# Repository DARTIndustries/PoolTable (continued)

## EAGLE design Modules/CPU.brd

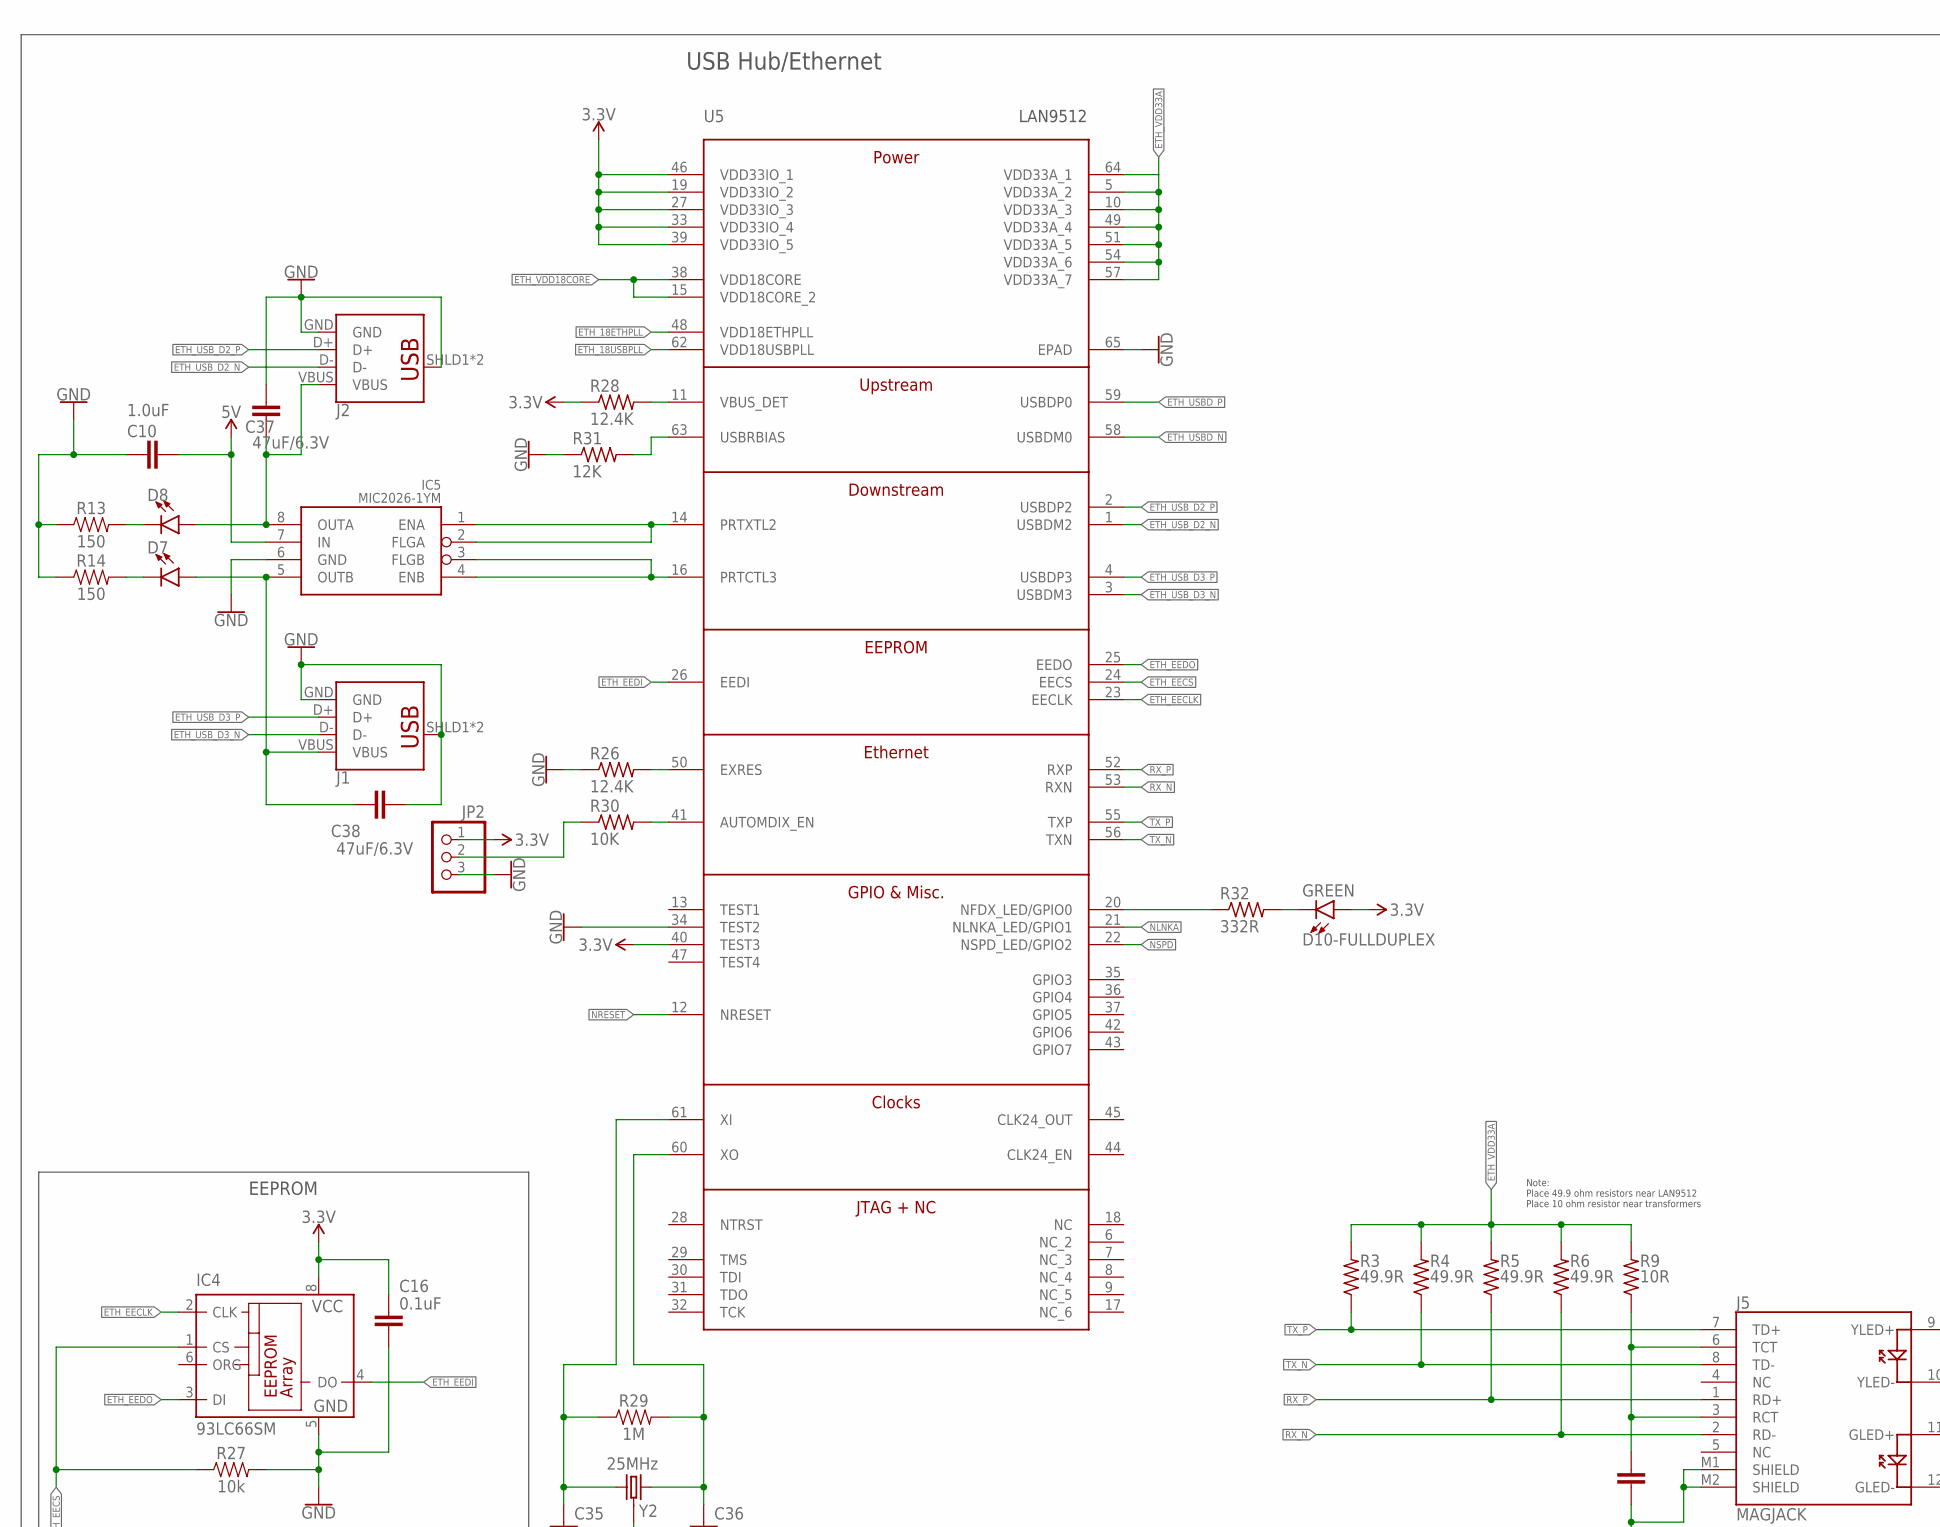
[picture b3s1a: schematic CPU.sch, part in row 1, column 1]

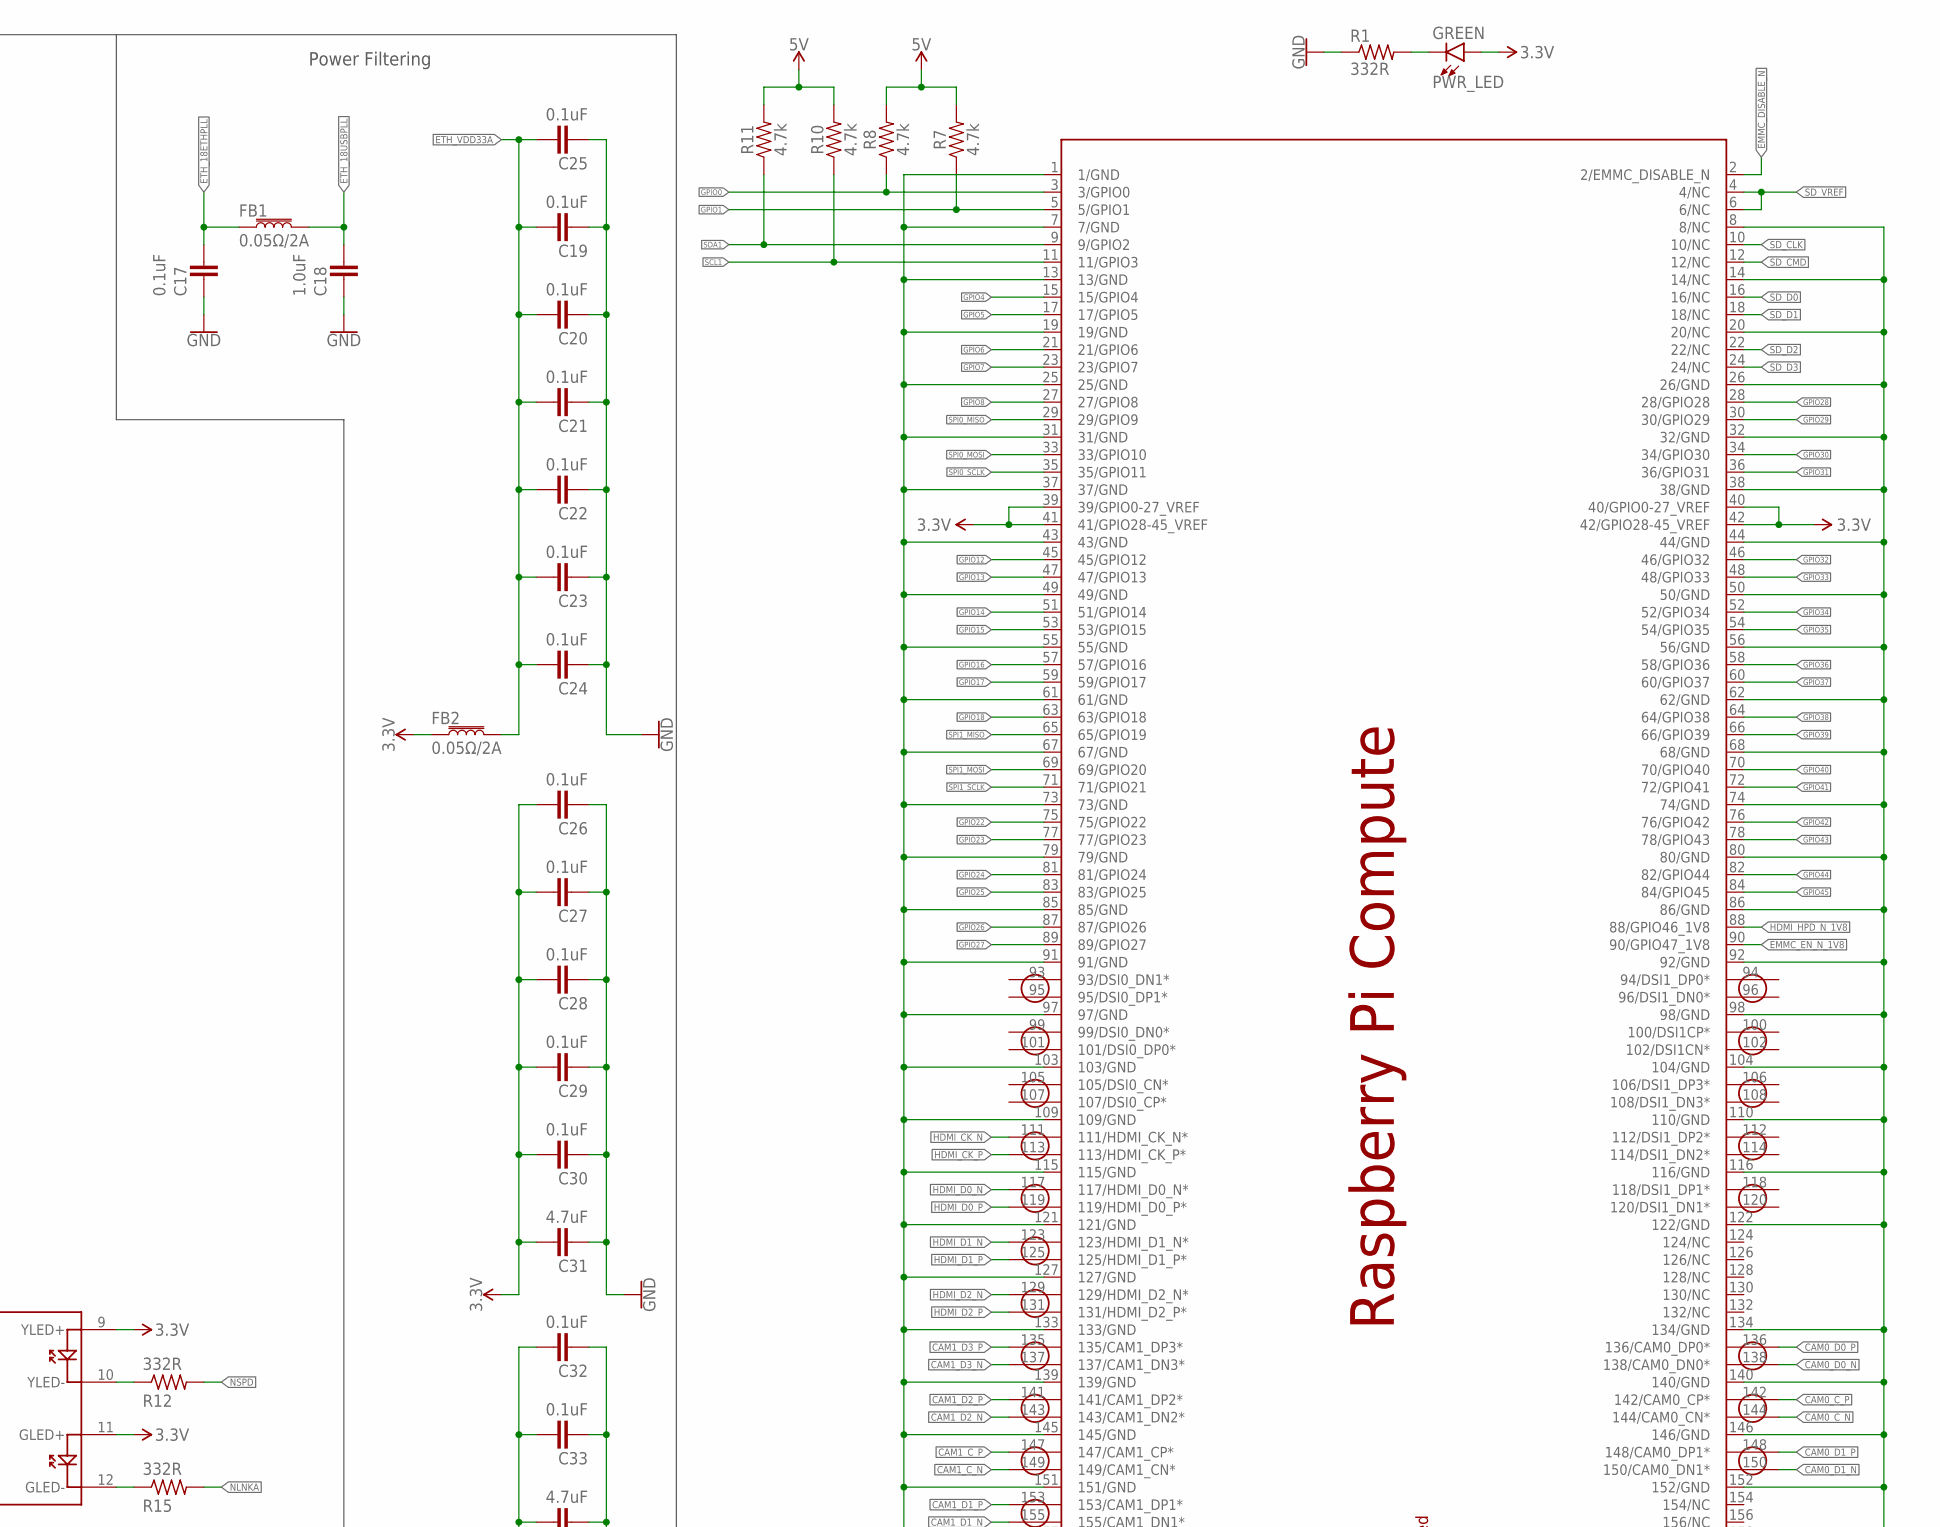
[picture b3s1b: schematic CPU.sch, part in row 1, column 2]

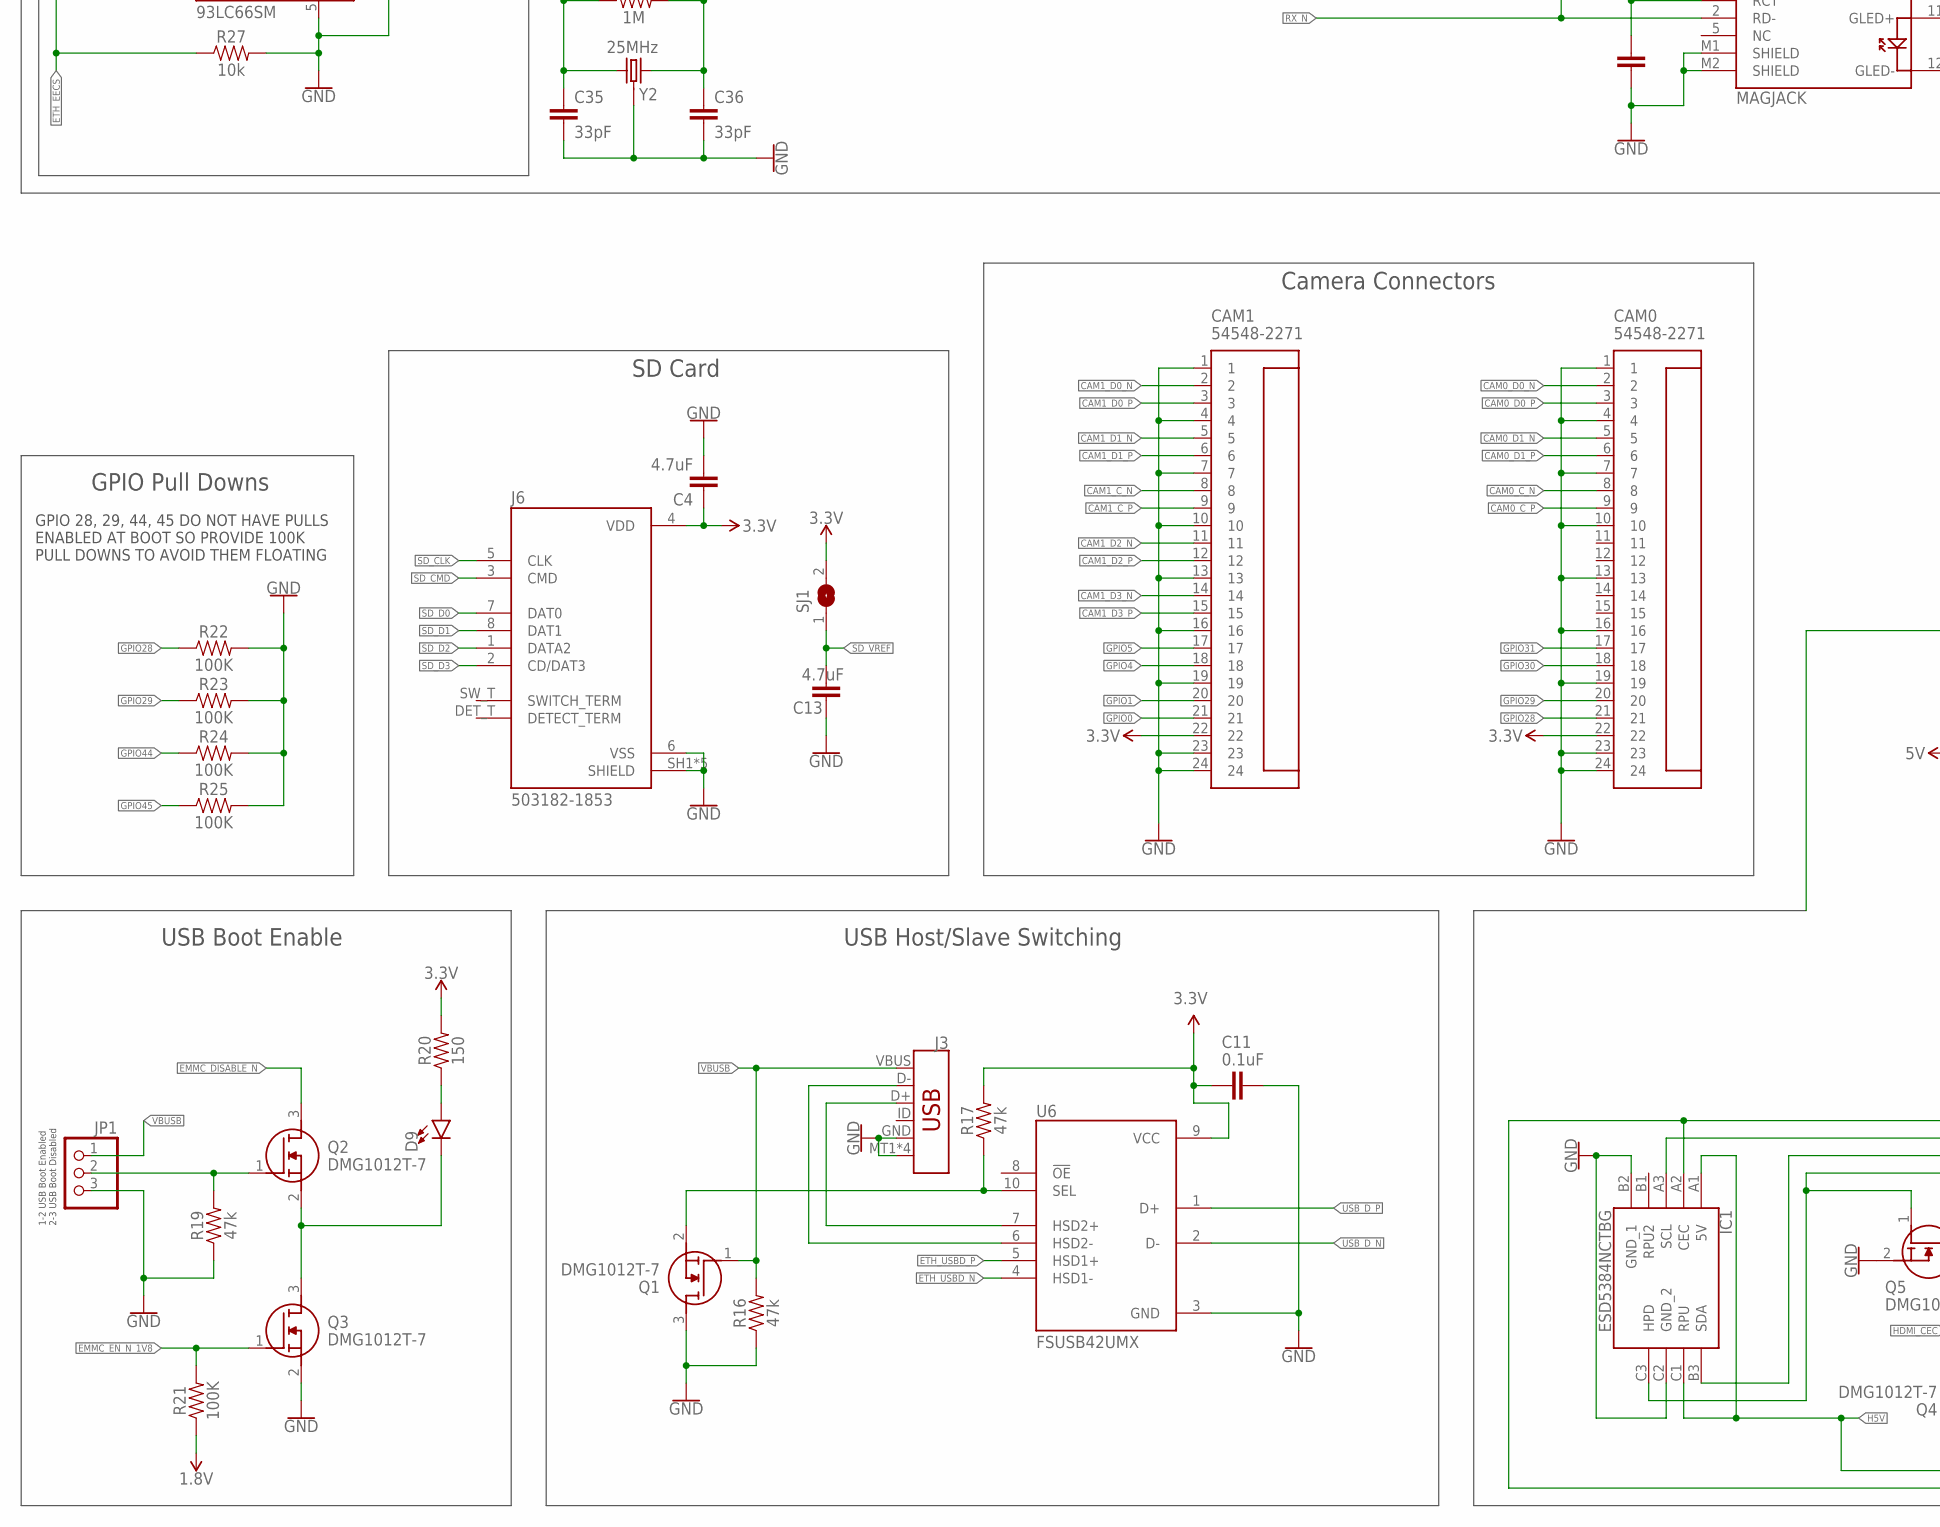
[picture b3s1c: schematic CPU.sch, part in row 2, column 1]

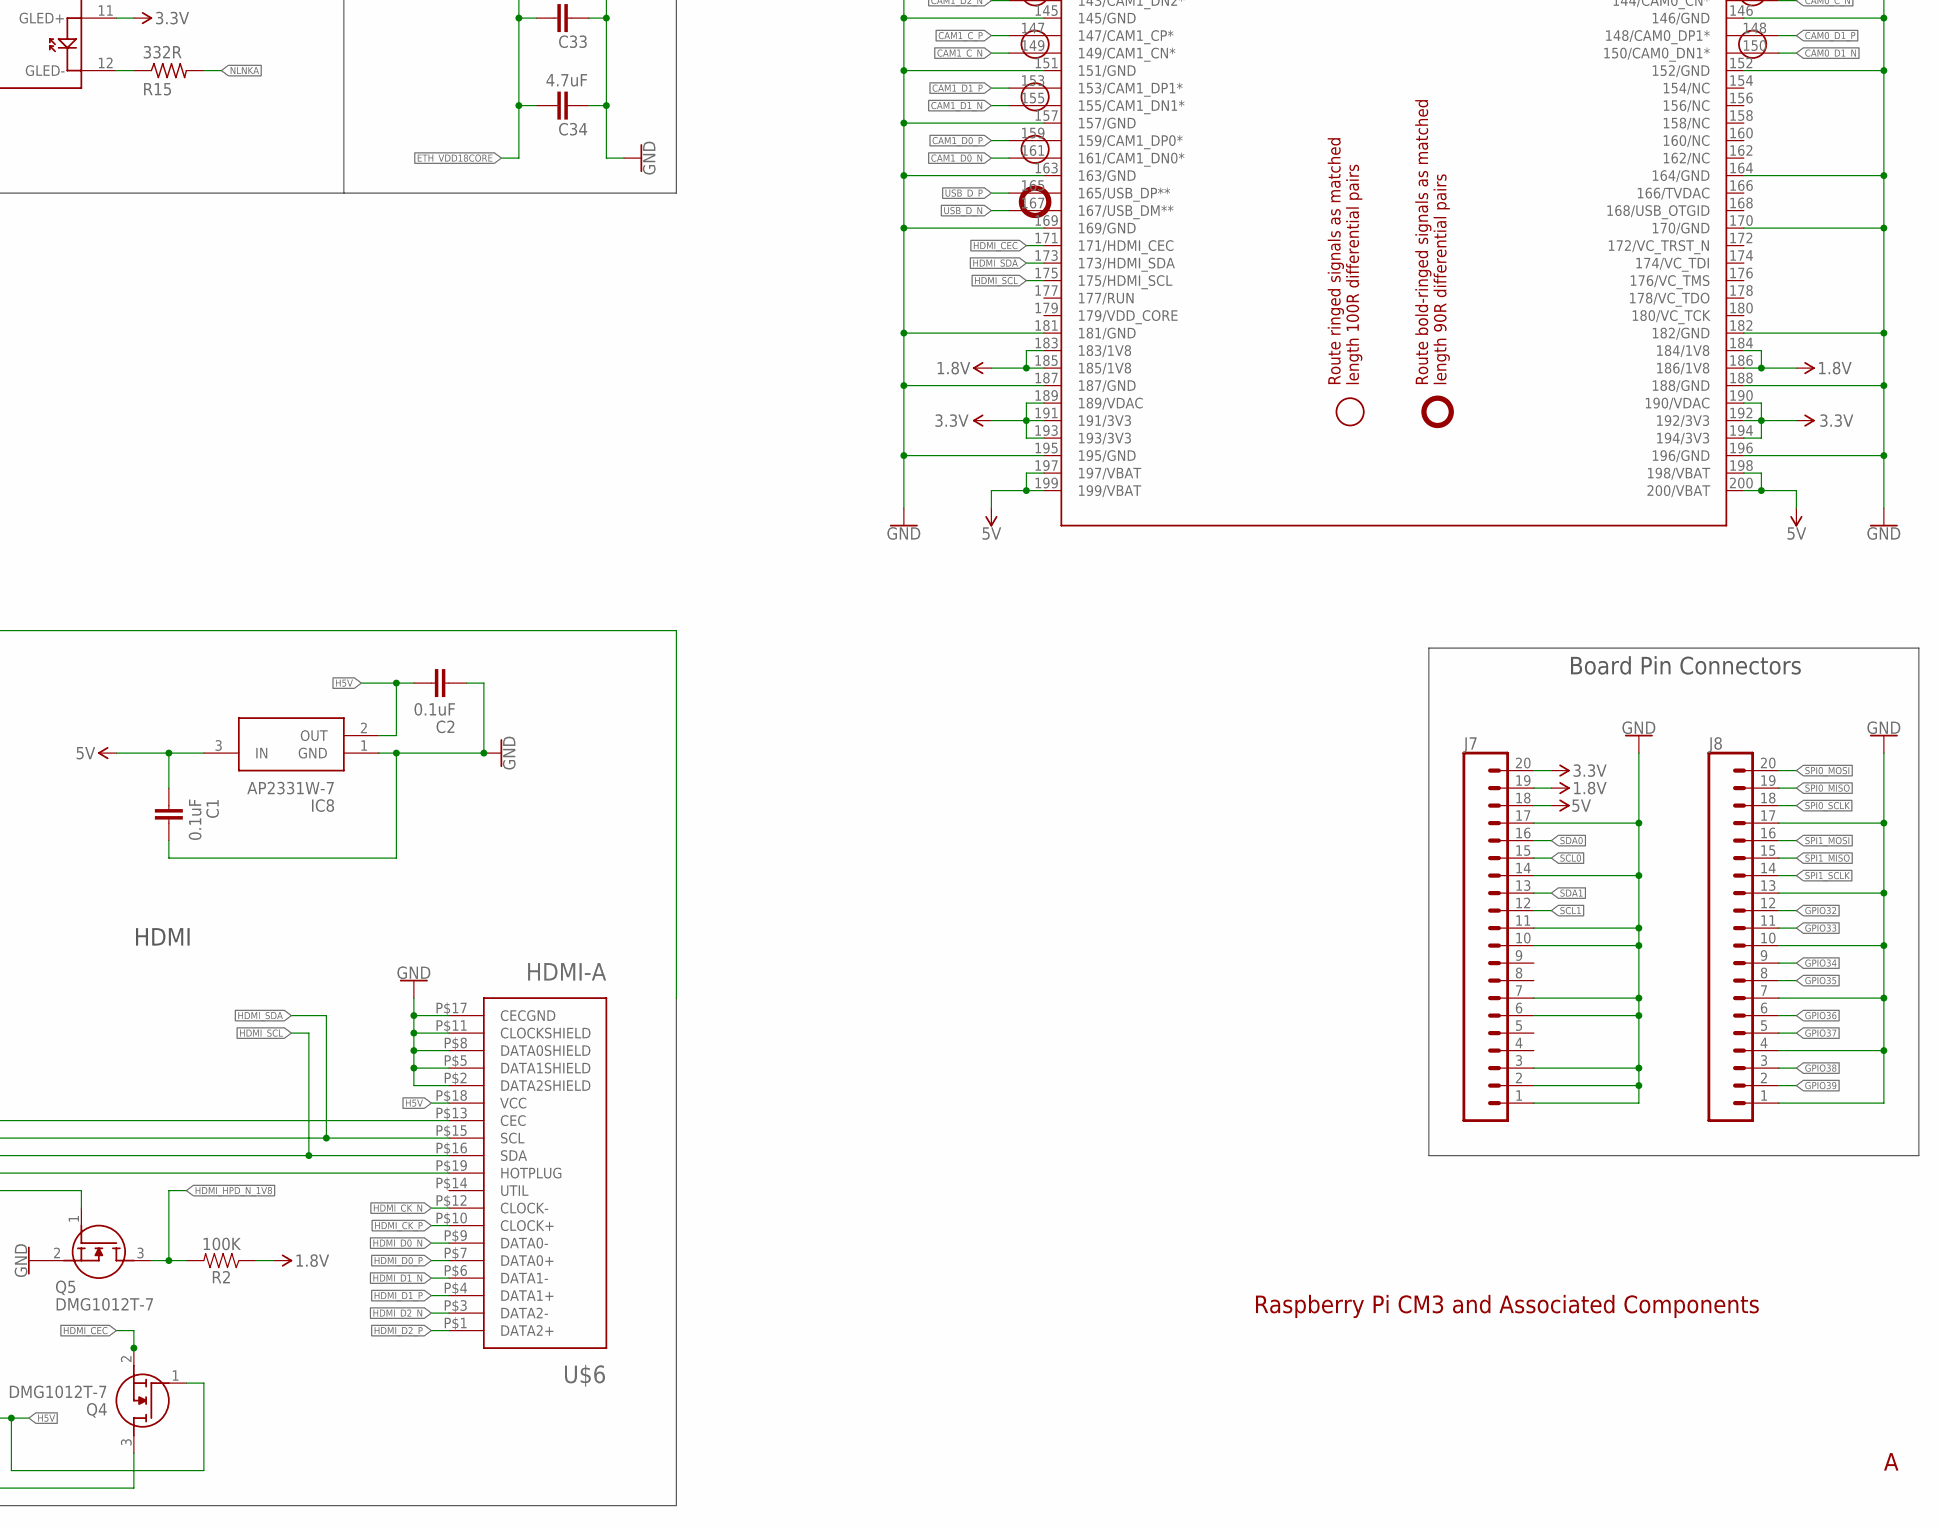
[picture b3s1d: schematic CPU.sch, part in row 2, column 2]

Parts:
C1, C2, C11, C16, C17, C19, C20, C21, C22, C23, C24, C25, C26, C27, C28, C29, C30, C32, C33: 0.1uF; 0402
C3: 0.022uF/50V; 0805
C4, C13: 4.7uF; 0603
C10, C18: 1.0uF; 0402
C31, C34: 4.7uF; 0402
C35, C36: 33pF; 0603
C37, C38: 47uF/6.3V; 0805
CAM0, CAM1: 54548-2271; 545482271
CPU1: RPI_COMPUTE
D7, D8, D9, D10-FULLDUPLEX: GREEN; LED-0603
FB1, FB2: 0.05Ω/2A; 0603
IC1: ESD5384NCTBG; BGA9C40P3X3_114X114X63
IC4: 93LC66SM; SO-08M
IC5: MIC2026-1YM; SO08
IC8: AP2331W-7; SOT95P285X130-3N
J1, J2: USB_A_SMT_FEMALE; USB-A-S-SILK-FEMALE
J3: USB_MICRO-B_SMT; USB-MICROB
J5: MAGJACK
J6: 503182-1853; MOLEX_503182-1853
J7, J8: CONN_20; 1X20
JP1, JP2: PINHD-1X3; 1X03
PWR_LED: GREEN; LED-0603
Q1, Q2, Q3, Q4, Q5: DMG1012T-7; SOT50P160X80-3N
R1, R12, R15, R32: 332R; R0603
R2, R21, R22, R23, R24, R25: 100K; 0402
R3, R4, R5, R6: 49.9R; R0603
R7, R8, R10, R11: 4.7k; 0603
R9: 10R; R0603
R13, R14, R20: 150; 0603
R16, R17, R19: 47k; 0603
R26, R28: 12.4K; R0603
R27: 10k; 0603
R29: 1M; 0603
R30: 10K; R0603
R31: 12K; R0603
SJ1: SJ
U5: LAN9512-JZX; QFN64_9X9MC
U6: FSUSB42UMX; IC_FSUSB42UMX
U$6: HDMI-A; HDMI_A
Y2: 25MHz; CRYSTAL-SMD-3.2X2.5MM

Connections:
1.8V: CPU1.183 (183/1V8), CPU1.184 (184/1V8), CPU1.185 (185/1V8), CPU1.186 (186/1V8), J7.19, R2.1, R21.1
3.3V: C4.1, C11.2, C16.1, C26.2, C27.2, C28.2, C29.2, C30.2, C31.2, CAM0.22, CAM1.22, CPU1.39 (39/GPIO0-27_VREF), CPU1.40 (40/GPIO0-27_VREF), CPU1.41 (41/GPIO28-45_VREF), CPU1.42 (42/GPIO28-45_VREF), CPU1.189 (189/VDAC), CPU1.190 (190/VDAC), CPU1.191 (191/3V3), CPU1.192 (192/3V3), CPU1.193 (193/3V3), CPU1.194 (194/3V3), D10-FULLDUPLEX.A, FB2.1, IC4.8 (VCC), J5.9 (YLED+), J5.11 (GLED+), J6.4 (VDD), J7.20, JP2.1, PWR_LED.A, R17.2, R20.2, R28.1, SJ1.2, U5.19 (VDD33IO_2), U5.27 (VDD33IO_3), U5.33 (VDD33IO_4), U5.39 (VDD33IO_5), U5.40 (TEST3), U5.46 (VDD33IO_1), U6.9 (VCC)
5V: C1.2, C10.2, CPU1.197 (197/VBAT), CPU1.198 (198/VBAT), CPU1.199 (199/VBAT), CPU1.200 (200/VBAT), IC5.7 (IN), IC8.3 (IN), J7.18, R7.2, R8.2, R10.2, R11.2
CAM0_C_N: CAM0.8, CPU1.144 (144/CAM0_CN*)
CAM0_C_P: CAM0.9, CPU1.142 (142/CAM0_CP*)
CAM0_D0_N: CAM0.2, CPU1.138 (138/CAM0_DN0*)
CAM0_D0_P: CAM0.3, CPU1.136 (136/CAM0_DP0*)
CAM0_D1_N: CAM0.5, CPU1.150 (150/CAM0_DN1*)
CAM0_D1_P: CAM0.6, CPU1.148 (148/CAM0_DP1*)
CAM1_C_N: CAM1.8, CPU1.149 (149/CAM1_CN*)
CAM1_C_P: CAM1.9, CPU1.147 (147/CAM1_CP*)
CAM1_D0_N: CAM1.2, CPU1.161 (161/CAM1_DN0*)
CAM1_D0_P: CAM1.3, CPU1.159 (159/CAM1_DP0*)
CAM1_D1_N: CAM1.5, CPU1.155 (155/CAM1_DN1*)
CAM1_D1_P: CAM1.6, CPU1.153 (153/CAM1_DP1*)
CAM1_D2_N: CAM1.11, CPU1.143 (143/CAM1_DN2*)
CAM1_D2_P: CAM1.12, CPU1.141 (141/CAM1_DP2*)
CAM1_D3_N: CAM1.14, CPU1.137 (137/CAM1_DN3*)
CAM1_D3_P: CAM1.15, CPU1.135 (135/CAM1_DP3*)
EMMC_DISABLE_N: CPU1.2 (2/EMMC_DISABLE_N), Q2.3 (D)
EMMC_EN_N_1V8: CPU1.90 (90/GPIO47_1V8), Q3.1 (G), R21.2
ETH_18ETHPLL: C17.2, FB1.1, U5.48 (VDD18ETHPLL)
ETH_18USBPLL: C18.2, FB1.2, U5.62 (VDD18USBPLL)
ETH_EECLK: IC4.2 (CLK), U5.23 (EECLK)
ETH_EECS: IC4.1 (CS), R27.1, U5.24 (EECS)
ETH_EEDI: IC4.4 (DO), U5.26 (EEDI)
ETH_EEDO: IC4.3 (DI), U5.25 (EEDO)
ETH_PWR2: C37.1, D8.A, IC5.8 (OUTA), J2.VBUS
ETH_PWR3: C38.1, D7.A, IC5.5 (OUTB), J1.VBUS
ETH_USBD_N: U5.58 (USBDM0), U6.4 (HSD1-)
ETH_USBD_P: U5.59 (USBDP0), U6.5 (HSD1+)
ETH_USB_D2_N: J2.D-, U5.1 (USBDM2)
ETH_USB_D2_P: J2.D+, U5.2 (USBDP2)
ETH_USB_D3_N: J1.D-, U5.3 (USBDM3)
ETH_USB_D3_P: J1.D+, U5.4 (USBDP3)
ETH_VDD18CORE: C32.2, C33.2, C34.2, U5.15 (VDD18CORE_2), U5.38 (VDD18CORE)
ETH_VDD33A: C19.2, C20.2, C21.2, C22.2, C23.2, C24.2, C25.2, FB2.2, R3.2, R4.2, R5.2, R6.2, R9.2, U5.5 (VDD33A_2), U5.10 (VDD33A_3), U5.49 (VDD33A_4), U5.51 (VDD33A_5), U5.54 (VDD33A_6), U5.57 (VDD33A_7), U5.64 (VDD33A_1)
GND: C1.1, C2.2, C3.1, C4.2, C10.1, C11.1, C13.1, C16.2, C17.1, C18.1, C19.1, C20.1, C21.1, C22.1, C23.1, C24.1, C25.1, C26.1, C27.1, C28.1, C29.1, C30.1, C31.1, C32.1, C33.1, C34.1, C35.2, C36.2, C37.2, C38.2, CAM0.1, CAM0.4, CAM0.7, CAM0.10, CAM0.13, CAM0.16, CAM0.19, CAM0.23, CAM0.24, CAM1.1, CAM1.4, CAM1.7, CAM1.10, CAM1.13, CAM1.16, CAM1.19, CAM1.23, CAM1.24, CPU1.1 (1/GND), CPU1.7 (7/GND), CPU1.8 (8/NC), CPU1.13 (13/GND), CPU1.14 (14/NC), CPU1.19 (19/GND), CPU1.20 (20/NC), CPU1.25 (25/GND), CPU1.26 (26/GND), CPU1.31 (31/GND), CPU1.32 (32/GND), CPU1.37 (37/GND), CPU1.38 (38/GND), CPU1.43 (43/GND), CPU1.44 (44/GND), CPU1.49 (49/GND), CPU1.50 (50/GND), CPU1.55 (55/GND), CPU1.56 (56/GND), CPU1.61 (61/GND), CPU1.62 (62/GND), CPU1.67 (67/GND), CPU1.68 (68/GND), CPU1.73 (73/GND), CPU1.74 (74/GND), CPU1.79 (79/GND), CPU1.80 (80/GND), CPU1.85 (85/GND), CPU1.86 (86/GND), CPU1.91 (91/GND), CPU1.92 (92/GND), CPU1.97 (97/GND), CPU1.98 (98/GND), CPU1.103 (103/GND), CPU1.104 (104/GND), CPU1.109 (109/GND), CPU1.110 (110/GND), CPU1.115 (115/GND), CPU1.116 (116/GND), CPU1.121 (121/GND), CPU1.122 (122/GND), CPU1.127 (127/GND), CPU1.133 (133/GND), CPU1.134 (134/GND), CPU1.139 (139/GND), CPU1.140 (140/GND), CPU1.145 (145/GND), CPU1.146 (146/GND), CPU1.151 (151/GND), CPU1.152 (152/GND), CPU1.157 (157/GND), CPU1.163 (163/GND), CPU1.164 (164/GND), CPU1.169 (169/GND), CPU1.170 (170/GND), CPU1.181 (181/GND), CPU1.182 (182/GND), CPU1.187 (187/GND), CPU1.188 (188/GND), CPU1.195 (195/GND), CPU1.196 (196/GND), IC1.B2 (GND_1), IC1.C2 (GND_2), IC4.5 (GND), IC5.6 (GND), IC8.1 (GND), J1.GND, J1.SHLD1 (SHIELD), J1.SHLD2 (SHIELD), J2.GND, J2.SHLD1 (SHIELD), J2.SHLD2 (SHIELD), J3.GND, J3.MT1 (SHIELD), J3.MT2 (SHIELD), J3.P$1 (SHIELD), J3.P$2 (SHIELD), J5.M1 (SHIELD), J5.M2 (SHIELD), J6.6 (VSS), J6.SH1 (SHIELD), J6.SH2 (SHIELD), J6.SH3 (SHIELD), J6.SH4 (SHIELD), J6.SH5 (SHIELD), J7.1, J7.2, J7.3, J7.6, J7.7, J7.10, J7.11, J7.14, J7.17, J8.1, J8.4, J8.7, J8.10, J8.13, J8.17, JP1.3, JP2.3, Q1.3 (D), Q3.2 (S), Q5.2 (S), R1.1, R13.1, R14.1, R16.1, R19.1, R22.2, R23.2, R24.2, R25.2, R26.1, R27.2, R31.1, U5.34 (TEST2), U5.65 (EPAD), U6.3 (GND), U$6.P$2 (DATA2SHIELD), U$6.P$5 (DATA1SHIELD), U$6.P$8 (DATA0SHIELD), U$6.P$11 (CLOCKSHIELD), U$6.P$17 (CECGND), Y2.2 (3), Y2.4 (3)
GPIO0: CAM1.21, CPU1.3 (3/GPIO0), R8.1
GPIO1: CAM1.20, CPU1.5 (5/GPIO1), R7.1
GPIO4: CAM1.18, CPU1.15 (15/GPIO4)
GPIO5: CAM1.17, CPU1.17 (17/GPIO5)
GPIO6: CPU1.21 (21/GPIO6)
GPIO7: CPU1.23 (23/GPIO7)
GPIO8: CPU1.27 (27/GPIO8)
GPIO12: CPU1.45 (45/GPIO12)
GPIO13: CPU1.47 (47/GPIO13)
GPIO14: CPU1.51 (51/GPIO14)
GPIO15: CPU1.53 (53/GPIO15)
GPIO16: CPU1.57 (57/GPIO16)
GPIO17: CPU1.59 (59/GPIO17)
GPIO18: CPU1.63 (63/GPIO18)
GPIO22: CPU1.75 (75/GPIO22)
GPIO23: CPU1.77 (77/GPIO23)
GPIO24: CPU1.81 (81/GPIO24)
GPIO25: CPU1.83 (83/GPIO25)
GPIO26: CPU1.87 (87/GPIO26)
GPIO27: CPU1.89 (89/GPIO27)
GPIO28: CAM0.21, CPU1.28 (28/GPIO28), R22.1
GPIO29: CAM0.20, CPU1.30 (30/GPIO29), R23.1
GPIO30: CAM0.18, CPU1.34 (34/GPIO30)
GPIO31: CAM0.17, CPU1.36 (36/GPIO31)
GPIO32: CPU1.46 (46/GPIO32), J8.12
GPIO33: CPU1.48 (48/GPIO33), J8.11
GPIO34: CPU1.52 (52/GPIO34), J8.9
GPIO35: CPU1.54 (54/GPIO35), J8.8
GPIO36: CPU1.58 (58/GPIO36), J8.6
GPIO37: CPU1.60 (60/GPIO37), J8.5
GPIO38: CPU1.64 (64/GPIO38), J8.3
GPIO39: CPU1.66 (66/GPIO39), J8.2
GPIO40: CPU1.70 (70/GPIO40)
GPIO41: CPU1.72 (72/GPIO41)
GPIO42: CPU1.76 (76/GPIO42)
GPIO43: CPU1.78 (78/GPIO43)
GPIO44: CPU1.82 (82/GPIO44), R24.1
GPIO45: CPU1.84 (84/GPIO45), R25.1
H5V: C2.1, IC1.A1 (5V), IC1.C1 (RPU), IC8.2 (OUT), Q4.1 (G), U$6.P$18 (VCC)
HDMI_CEC: CPU1.171 (171/HDMI_CEC), Q4.2 (S)
HDMI_CK_N: CPU1.111 (111/HDMI_CK_N*), U$6.P$12 (CLOCK-)
HDMI_CK_P: CPU1.113 (113/HDMI_CK_P*), U$6.P$10 (CLOCK+)
HDMI_D0_N: CPU1.117 (117/HDMI_D0_N*), U$6.P$9 (DATA0-)
HDMI_D0_P: CPU1.119 (119/HDMI_D0_P*), U$6.P$7 (DATA0+)
HDMI_D1_N: CPU1.123 (123/HDMI_D1_N*), U$6.P$6 (DATA1-)
HDMI_D1_P: CPU1.125 (125/HDMI_D1_P*), U$6.P$4 (DATA1+)
HDMI_D2_N: CPU1.129 (129/HDMI_D2_N*), U$6.P$3 (DATA2-)
HDMI_D2_P: CPU1.131 (131/HDMI_D2_P*), U$6.P$1 (DATA2+)
HDMI_HPD_N_1V8: CPU1.88 (88/GPIO46_1V8), Q5.3 (D), R2.2
HDMI_SCL: CPU1.175 (175/HDMI_SCL), IC1.B3 (SDA), U$6.P$16 (SDA)
HDMI_SDA: CPU1.173 (173/HDMI_SDA), IC1.A3 (SCL), U$6.P$15 (SCL)
unnamed: PWR_LED.C, R1.2
unnamed: C3.2, J5.3 (RCT), J5.6 (TCT), R9.1
unnamed: R26.2, U5.50 (EXRES)
unnamed: R28.2, U5.11 (VBUS_DET)
unnamed: IC1.C3 (HPD), Q5.1 (G), U$6.P$19 (HOTPLUG)
unnamed: C35.1, R29.1, U5.61 (XI), Y2.1
unnamed: C36.1, R29.2, U5.60 (XO), Y2.3 (2)
unnamed: IC1.A2 (CEC), Q4.3 (D), U$6.P$13 (CEC)
unnamed: IC5.1 (ENA), IC5.2 (FLGA), U5.14 (PRTXTL2)
unnamed: IC5.3 (FLGB), IC5.4 (ENB), U5.16 (PRTCTL3)
unnamed: J5.10 (YLED-), R12.1
unnamed: R30.2, U5.41 (AUTOMDIX_EN)
unnamed: JP2.2, R30.1
unnamed: J5.12 (GLED-), R15.1
unnamed: D8.C, R13.2
unnamed: D7.C, R14.2
unnamed: J3.D+, U6.7 (HSD2+)
unnamed: Q1.2 (S), R17.1, U6.10 (SEL)
unnamed: J3.D-, U6.6 (HSD2-)
unnamed: JP1.2, Q2.1 (G), R19.2
unnamed: D9.C, Q2.2 (S), Q3.3 (D)
unnamed: D9.A, R20.1
unnamed: R31.2, U5.63 (USBRBIAS)
unnamed: D10-FULLDUPLEX.C, R32.2
unnamed: R32.1, U5.20 (NFDX_LED/GPIO0)
NLNKA: R15.2, U5.21 (NLNKA_LED/GPIO1)
NRESET: U5.12 (NRESET)
NSPD: R12.2, U5.22 (NSPD_LED/GPIO2)
RX_N: J5.2 (RD-), R6.1, U5.53 (RXN)
RX_P: J5.1 (RD+), R5.1, U5.52 (RXP)
SCL0: J7.15
SCL1: CPU1.11 (11/GPIO3), J7.12, R10.1
SDA0: J7.16
SDA1: CPU1.9 (9/GPIO2), J7.13, R11.1
SD_CLK: CPU1.10 (10/NC), J6.5 (CLK)
SD_CMD: CPU1.12 (12/NC), J6.3 (CMD)
SD_D0: CPU1.16 (16/NC), J6.7 (DAT0)
SD_D1: CPU1.18 (18/NC), J6.8 (DAT1)
SD_D2: CPU1.22 (22/NC), J6.1 (DATA2)
SD_D3: CPU1.24 (24/NC), J6.2 (CD/DAT3)
SD_VREF: C13.2, CPU1.4 (4/NC), CPU1.6 (6/NC), SJ1.1
SPI0_MISO: CPU1.29 (29/GPIO9), J8.19
SPI0_MOSI: CPU1.33 (33/GPIO10), J8.20
SPI0_SCLK: CPU1.35 (35/GPIO11), J8.18
SPI1_MISO: CPU1.65 (65/GPIO19), J8.15
SPI1_MOSI: CPU1.69 (69/GPIO20), J8.16
SPI1_SCLK: CPU1.71 (71/GPIO21), J8.14
TX_N: J5.8 (TD-), R4.1, U5.56 (TXN)
TX_P: J5.7 (TD+), R3.1, U5.55 (TXP)
USB_D_N: CPU1.167 (167/USB_DM**), U6.2 (D-)
USB_D_P: CPU1.165 (165/USB_DP**), U6.1 (D+)
VBUSB: J3.VBUS, JP1.1, Q1.1 (G), R16.2

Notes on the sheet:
USB Boot Enable
1-2 USB Boot Enabled 2-3 USB Boot Disabled
USB Host/Slave Switching
GPIO Pull Downs
SD Card
GPIO 28, 29, 44, 45 DO NOT HAVE PULLS ENABLED AT BOOT SO PROVIDE 100K PULL DOWNS TO AVOID THEM FLOATING
USB Hub/Ethernet
LAN9512
Camera Connectors
EEPROM
Power Filtering
Raspberry Pi CM3 and Associated Components
HDMI
Board Pin Connectors
Note: Place 49.9 ohm resistors near LAN9512 Place 10 ohm resistor near transformers

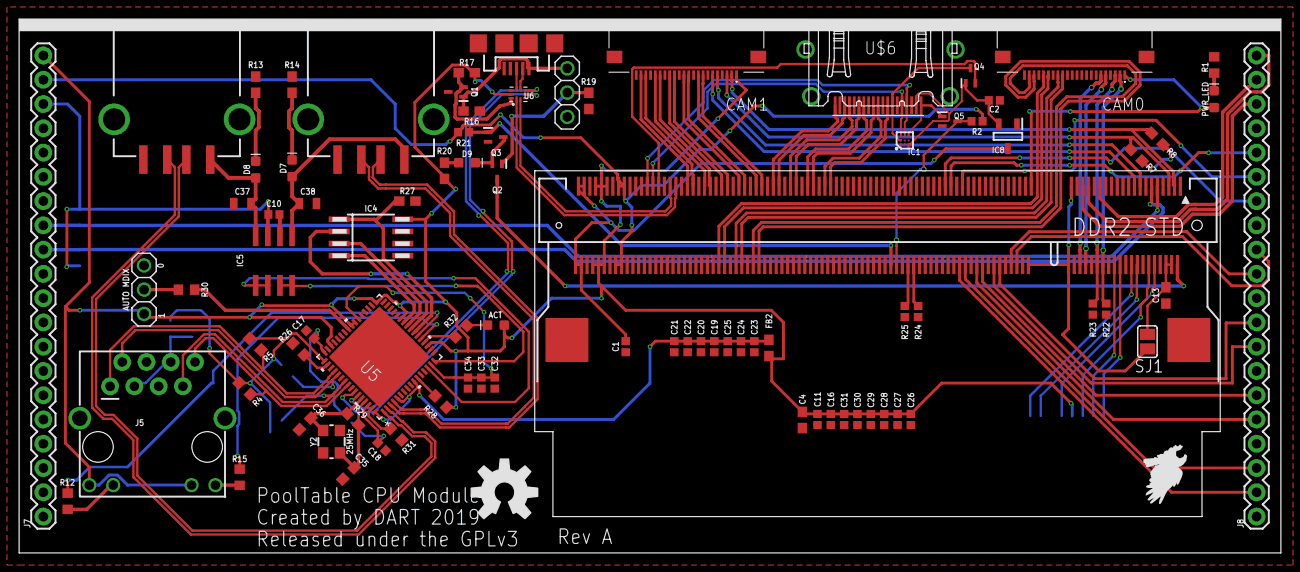
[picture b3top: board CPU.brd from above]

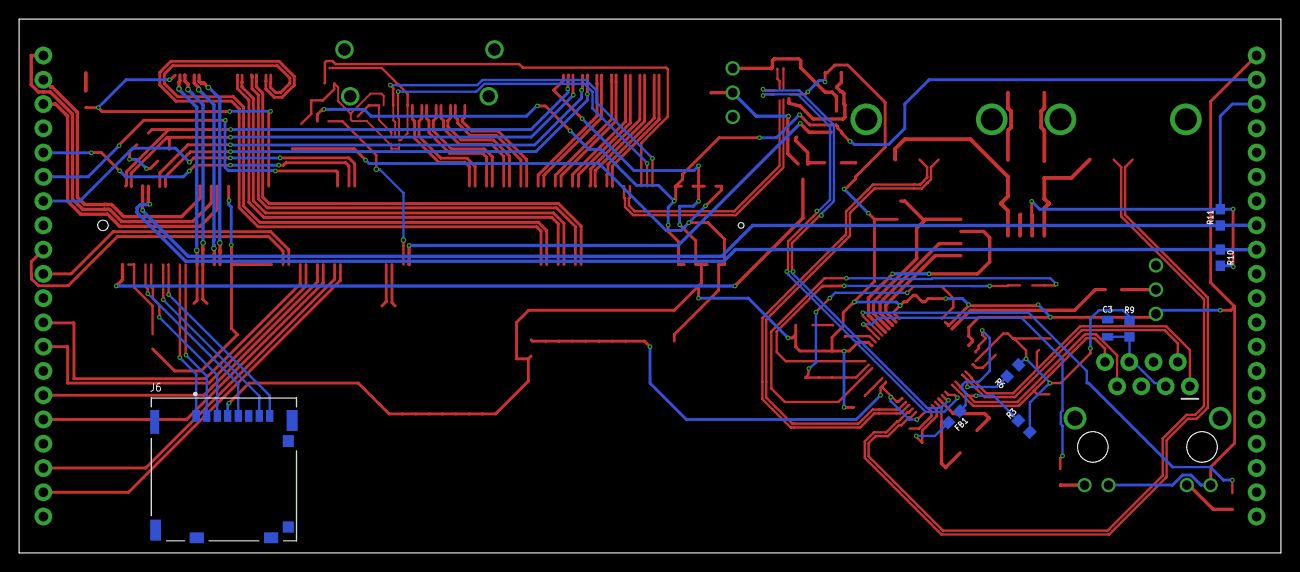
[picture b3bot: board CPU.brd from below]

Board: 2 copper layers, 132.1 x 55.9 mm, 95 parts (8 on the bottom side), 118 nets.

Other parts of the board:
U$1: OSHW-LOGO-L

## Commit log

2018-11-13 updated gitignore
2018-11-29 Added PWM Module
2018-11-29 Added frame
2018-11-30 Added modules library
2018-12-01 Added power supply
2019-01-12 Added four temp sensors
2019-01-19 Started work on USB Hub/Ethernet
2019-01-19 Implemented boot enable and finished USB
2019-01-19 Added Cam Header
2019-01-19 Cleaned up Schematic
2019-01-19 Updated Camera header
2019-01-19 Implementing Cameras
2019-01-19 Added ESD5384NCTBG
2019-01-19 First HDMI work
2019-01-20 Syncing work
2019-01-21 Added EEPROM for LAN9512
2019-01-21 Removed board file for now
2019-01-22 Duplicated CM3 and mostly finished USB hub
2019-01-26 Added CPU Module
2019-01-27 Updated CPU Module and Added Module to Library
2019-01-27 Updated CPU Module and removed components from Main Board
2019-01-27 Added Connectors and Molex
2019-01-29 Finished HDMI
2019-02-02 Ultafit library and OSH park rules
2019-02-02 Merged HDMI
2019-02-02 Added solder jumper for HDMI
2019-02-02 Work
2019-02-16 Fixed CAM connectors
2019-02-17 Got a lot of routing done
2019-02-23 More routing
2019-02-23 latest
2019-02-27 Sending PWM Module to Fab
2019-03-12 Auto stash before merge of "master" and "origin/master"
2019-03-22 pool table final
